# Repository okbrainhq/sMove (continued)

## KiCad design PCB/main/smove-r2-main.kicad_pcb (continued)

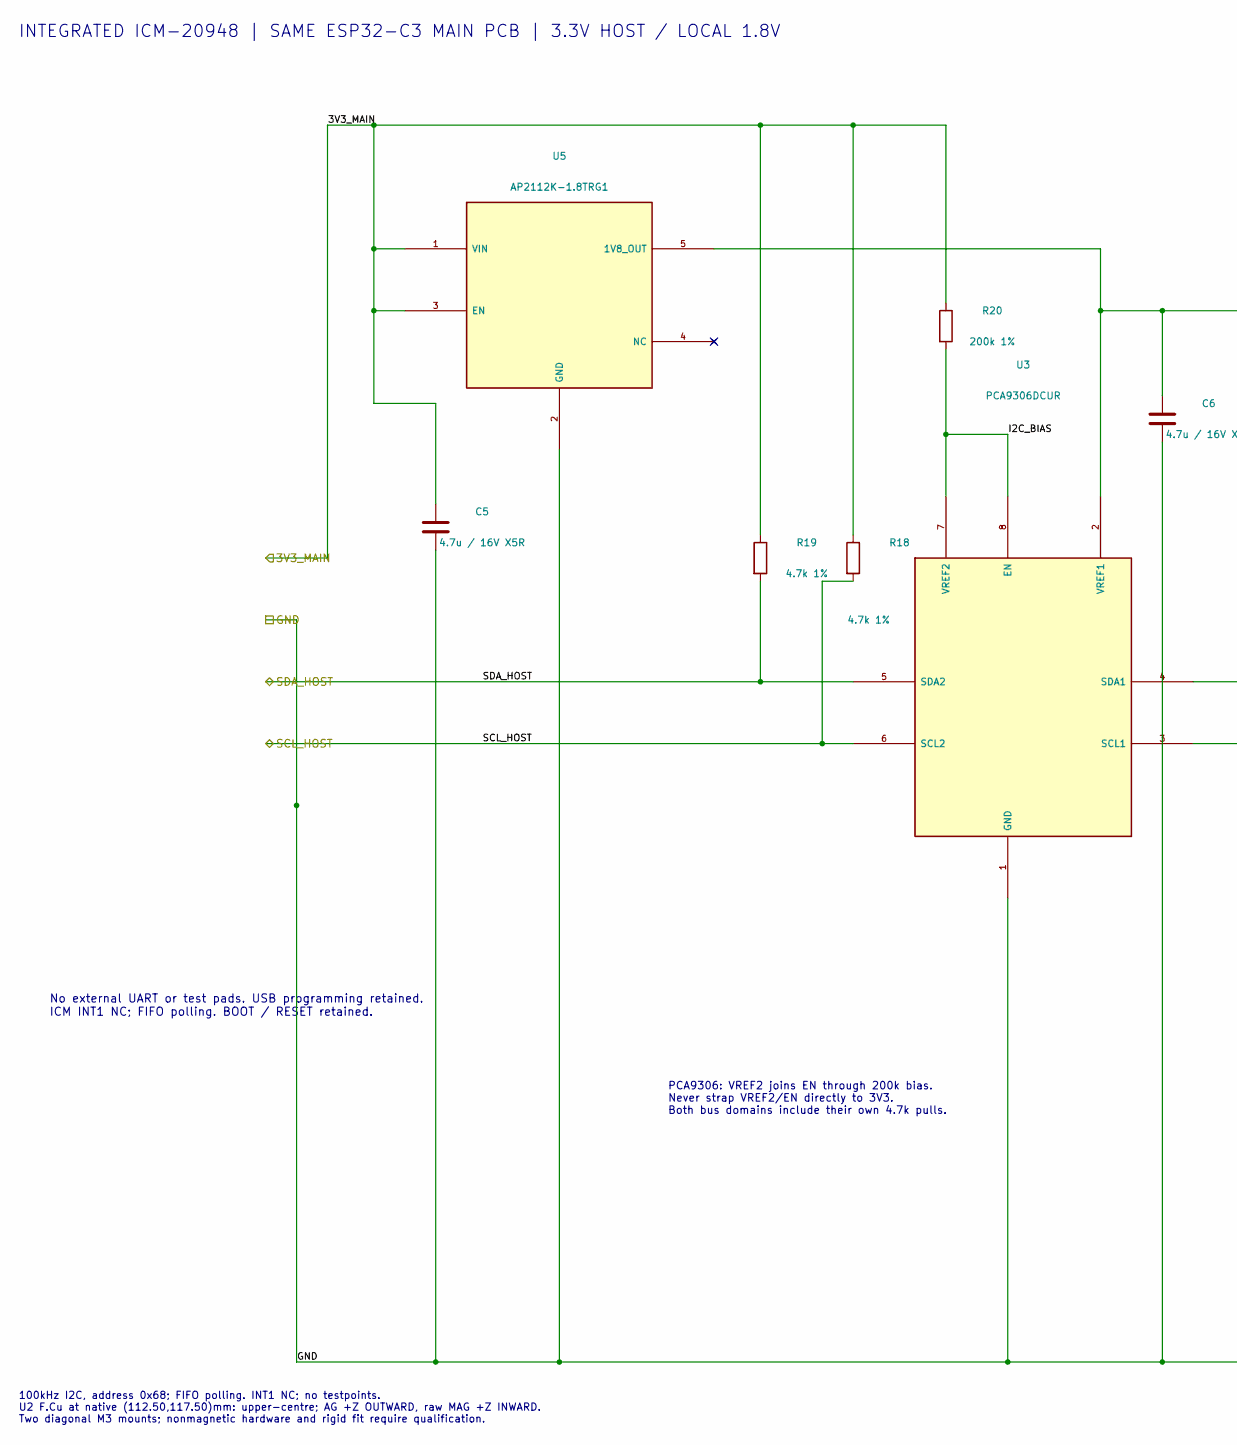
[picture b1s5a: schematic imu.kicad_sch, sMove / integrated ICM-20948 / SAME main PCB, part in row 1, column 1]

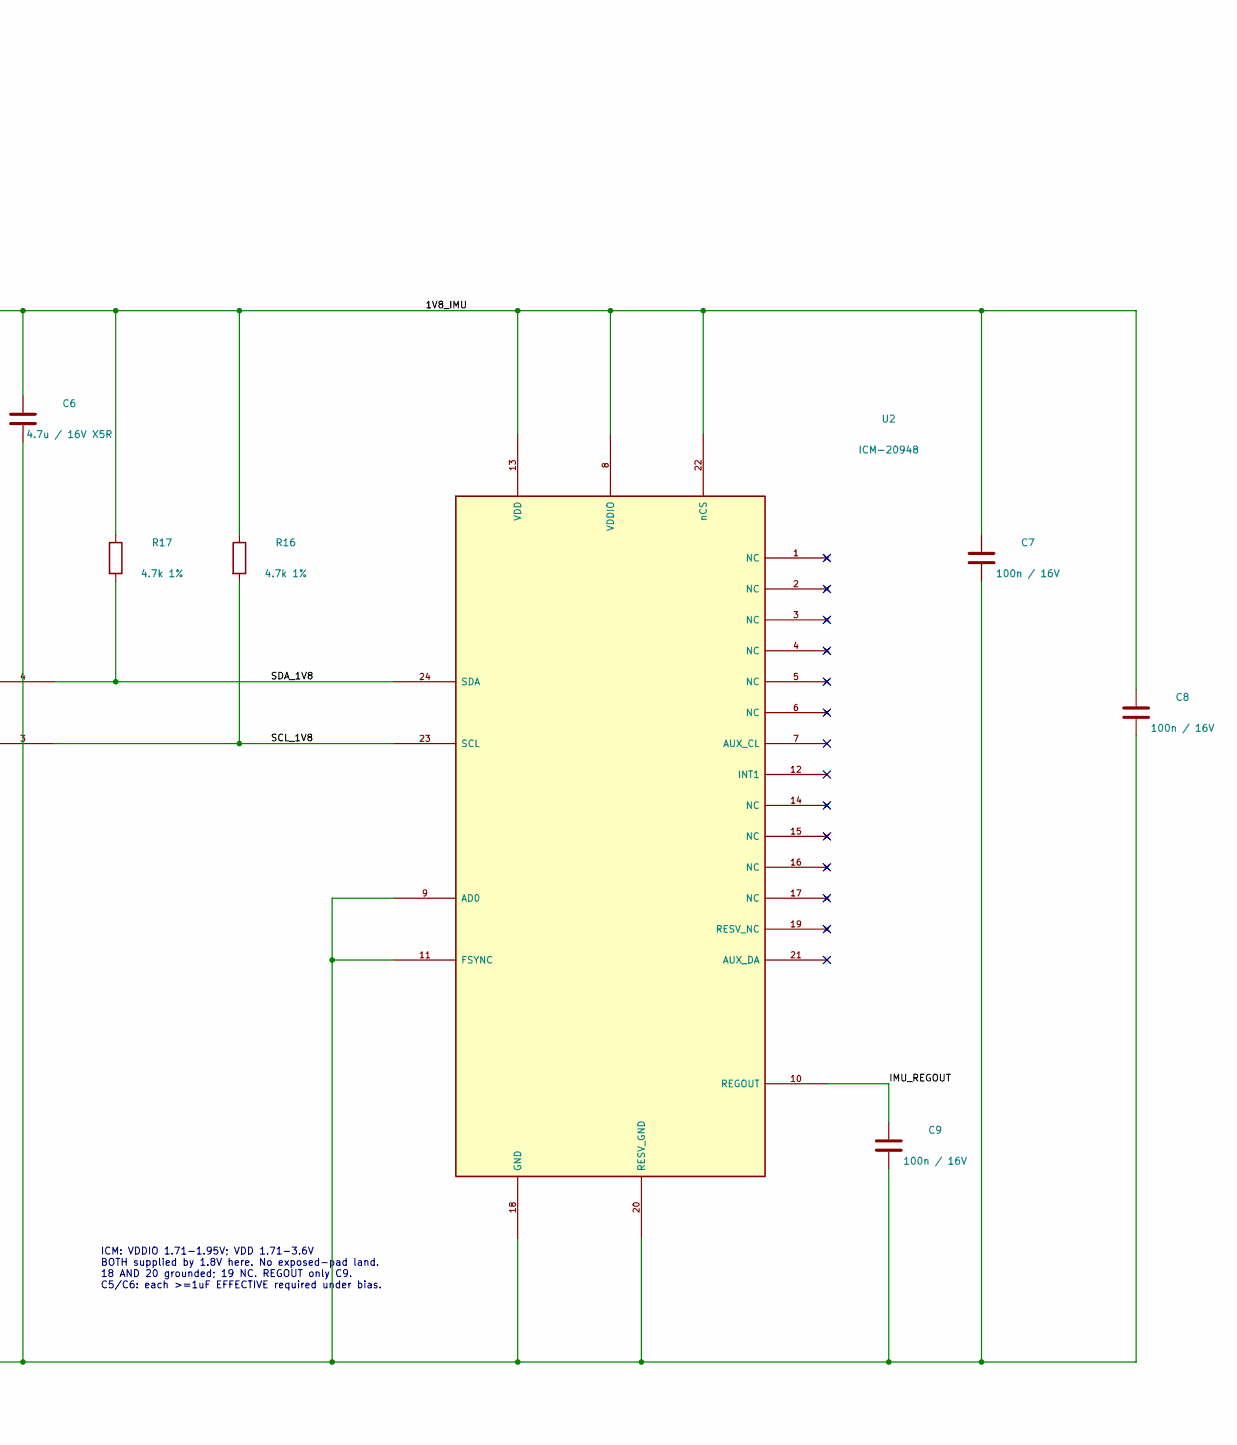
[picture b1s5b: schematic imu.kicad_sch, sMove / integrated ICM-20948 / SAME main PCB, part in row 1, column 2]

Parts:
C5, C6: 4.7u / 16V X5R; C_0603_1608Metric; MPN CL10A475KO8NNNC; LCSC C19666
C7, C8, C9: 100n / 16V; C_0402_1005Metric; MPN CL05B104KO5NNNC; LCSC C1525
R16, R17, R18, R19: 4.7k 1%; R_0402_1005Metric; MPN 0402WGF4701TCE; LCSC C25900
R20: 200k 1%; R_0402_1005Metric; MPN 0402WGF2003TCE; LCSC C25764
U2: ICM-20948; InvenSense_QFN-24_3x3mm_P0.4mm; MPN ICM-20948; LCSC C726001
U3: PCA9306DCUR; PCA9306_DCU0008A; MPN PCA9306DCUR; LCSC C33196
U5: AP2112K-1.8TRG1; SOT-23-5; MPN AP2112K-1.8TRG1; LCSC C176944

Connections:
/3V3_MAIN: C5.1, R18.1, R19.1, R20.1, U5.1 (VIN), U5.3 (EN); also elsewhere on the board
/IMU/1V8_IMU: C6.1, C7.1, C8.1, R16.1, R17.1, U2.8 (VDDIO), U2.13 (VDD), U2.22 (nCS), U3.2 (VREF1), U5.5 (1V8_OUT)
/IMU/I2C_BIAS: R20.2, U3.7 (VREF2), U3.8 (EN)
/IMU/IMU_REGOUT: C9.1, U2.10 (REGOUT)
/IMU/SCL_1V8: R16.2, U2.23 (SCL), U3.3 (SCL1)
/IMU/SDA_1V8: R17.2, U2.24 (SDA), U3.4 (SDA1)
/SCL_HOST: R18.2, U3.6 (SCL2); also elsewhere on the board
/SDA_HOST: R19.2, U3.5 (SDA2); also elsewhere on the board
GND: C5.2, C6.2, C7.2, C8.2, C9.2, U2.9 (AD0), U2.11 (FSYNC), U2.18 (GND), U2.20 (RESV_GND), U3.1 (GND), U5.2 (GND); also elsewhere on the board

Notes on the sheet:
INTEGRATED ICM-20948 | SAME ESP32-C3 MAIN PCB | 3.3V HOST / LOCAL 1.8V
No external UART or test pads. USB programming retained. ICM INT1 NC; FIFO polling. BOOT / RESET retained.
PCA9306: VREF2 joins EN through 200k bias. Never strap VREF2/EN directly to 3V3. Both bus domains include their own 4.7k pulls.
ICM: VDDIO 1.71-1.95V; VDD 1.71-3.6V BOTH supplied by 1.8V here. No exposed-pad land. 18 AND 20 grounded; 19 NC. REGOUT only C9. C5/C6: each >=1uF EFFECTIVE required under bias.
100kHz I2C, address 0x68; FIFO polling. INT1 NC; no testpoints. U2 F.Cu at native (112.50,117.50)mm: upper-centre; AG +Z OUTWARD, raw MAG +Z INWARD. Two diagonal M3 mounts; nonmagnetic hardware and rigid fit require qualification.

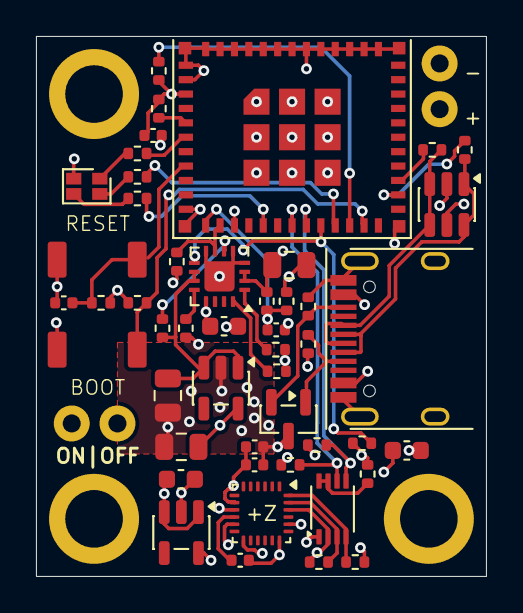
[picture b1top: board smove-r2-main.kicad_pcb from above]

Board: 4 copper layers, 25.0 x 30.0 mm, 53 parts (0 on the bottom side), 36 nets.

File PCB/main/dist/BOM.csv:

Comment,Designator,Footprint,LCSC Part #,Quantity,Manufacturer Part Number
4.7uF / 16V,"C1,C5,C6",C_0603_1608Metric,C19666,3,CL10A475KO8NNNC
47uF / 6.3V,"C2,C13",C_0805_2012Metric,C16780,2,CL21A476MQYNNNE
22uF / 10V,C3,C_0805_2012Metric,C29277,1,CL21A226MPQNNNE
100nF / 16V,"C4,C7,C8,C9,C11",C_0402_1005Metric,C1525,5,CL05B104KO5NNNC
1uF / 25V,C10,C_0402_1005Metric,C52923,1,CL05A105KA5NQNC
LTST-C19HE1WT / CA,D1,LED_LiteOn_LTST-C19HE1WT,C458749,1,LTST-C19HE1WT
TYPE-C-31-M-12,J1,USB_C_Receptacle_HRO_TYPE-C-31-M-12,C165948,1,TYPE-C-31-M-12
5.1k,"R1,R2",R_0402_1005Metric,C25905,2,0402WGF5101TCE
22R,"R3,R4",R_0402_1005Metric,C25092,2,0402WGF220JTCE
100k,"R5,R14,R15",R_0402_1005Metric,C25741,3,0402WGF1003TCE
10k,"R7,R8,R9,R10,R23",R_0402_1005Metric,C25744,5,0402WGF1002TCE
1k,"R11,R12,R13",R_0402_1005Metric,C11702,3,0402WGF1001TCE
4.7k 1%,"R16,R17,R18,R19,R22",R_0402_1005Metric,C25900,5,0402WGF4701TCE
200k 1%,R20,R_0402_1005Metric,C25764,1,0402WGF2003TCE
8.2k,R21,R_0402_1005Metric,C25924,1,0402WGF8201TCE
RESET,"SW2,SW3",TS1088,C720477,2,TS-1088-AR02016
ESP32-C3-MINI-1-N4,U1,ESP32-C3-MINI-1,C2838502,1,ESP32-C3-MINI-1-N4
ICM-20948,U2,InvenSense_QFN-24_3x3mm_P0.4mm,C726001,1,ICM-20948
PCA9306DCUR,U3,PCA9306_DCU0008A,C33196,1,PCA9306DCUR
AP2112K-3.3TRG1,U4,SOT-23-5,C51118,1,AP2112K-3.3TRG1
AP2112K-1.8TRG1,U5,SOT-23-5,C176944,1,AP2112K-1.8TRG1
BQ24074RGTR,U6,BQ24074_RGT,C54313,1,BQ24074RGTR
USBLC6-2SC6,U8,SOT-23-6,C7519,1,USBLC6-2SC6
"PESD5V0S2BT,215",U9,SOT-23,C49338,1,"PESD5V0S2BT,215"

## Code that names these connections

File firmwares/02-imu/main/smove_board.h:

// sMove board map — smove-r2-main (U1 = ESP32-C3-MINI-1-N4)
//
// User-interface RGB LED, D1 = LiteOn LTST-C19HE1WT (COMMON ANODE):
//
//   D1 pad 4 (common anode) -- 3V3_MAIN
//   D1 pad 1 (red   cathode) -- R11 1k -- U1 GPIO3  (net LED_R)
//   D1 pad 2 (green cathode) -- R12 1k -- U1 GPIO7  (net LED_G)
//   D1 pad 3 (blue  cathode) -- R13 1k -- U1 GPIO10 (net LED_B)
//
// The cathodes are pulled to 3V3 through the LED, so the GPIOs SINK current:
//   level 0 (low)  -> colour ON
//   level 1 (high) -> colour OFF
// All three pins must idle HIGH so the LED stays dark (including at reset,
// before the GPIO matrix is configured).
//
// 9-axis IMU, U2 = TDK InvenSense ICM-20948 (QFN-24 3x3 mm).
//
// The IMU core and its I/O rail run from 1V8_IMU (U5, AP2112K-1V8), so the I2C
// lines cross the PCA9306 level translator (U3) before reaching the C3:
//
//   U2 pad 24 (SDA) -- /IMU/SDA_1V8 -- U3 pad 4 || U3 pad 5 -- /SDA_HOST -- U1 pad 19 (GPIO5)
//   U2 pad 23 (SCL) -- /IMU/SCL_1V8 -- U3 pad 3 || U3 pad 6 -- /SCL_HOST -- U1 pad 18 (GPIO4)
//   U2 pad 22 (nCS)      -> 1V8_IMU  => I2C mode (not SPI)
//   U2 pad 12 (INT1)     not connected on this board — poll the data registers
//   U2 pad 10 (REGOUT)   -- C10 1uF, internal regulator, do not load
//
// Bus pull-ups: R16/R17 4.7k to 1V8_IMU on the IMU side, R18/R19 4.7k to
// 3V3_MAIN on the host side. Only the IMU sits on this bus.
//
// I2C address: measured 0x68 on the assembled board (AD0 low). The datasheet
// pair is 0x68/0x69, so the driver probes 0x68 and falls back to 0x69.
//
// The board underside faces the body and the IMU +Z axis stays outward (see the
// enclosure notes), so +Z reads ~+1 g when the unit rests on its back.
#pragma once

#include "driver/gpio.h"

#define SMOVE_LED_R_GPIO   GPIO_NUM_3
#define SMOVE_LED_G_GPIO   GPIO_NUM_7
#define SMOVE_LED_B_GPIO   GPIO_NUM_10

/* Common-anode LED: driving the pin low turns that colour on. */
#define SMOVE_LED_ON_LEVEL  0
#define SMOVE_LED_OFF_LEVEL 1

/* ICM-20948 on the 1.8 V I2C bus behind the PCA9306. */
#define SMOVE_IMU_SDA_GPIO        GPIO_NUM_5
#define SMOVE_IMU_SCL_GPIO        GPIO_NUM_4
#define SMOVE_IMU_I2C_ADDR        0x68   /* measured on smove-r2-main (AD0 low) */
#define SMOVE_IMU_I2C_ADDR_ALT    0x69   /* probe fallback (AD0 high / reworked board) */
#define SMOVE_IMU_I2C_SPEED_HZ    400000 /* bus supports 400 kHz; drop to 100 kHz if long leads */
